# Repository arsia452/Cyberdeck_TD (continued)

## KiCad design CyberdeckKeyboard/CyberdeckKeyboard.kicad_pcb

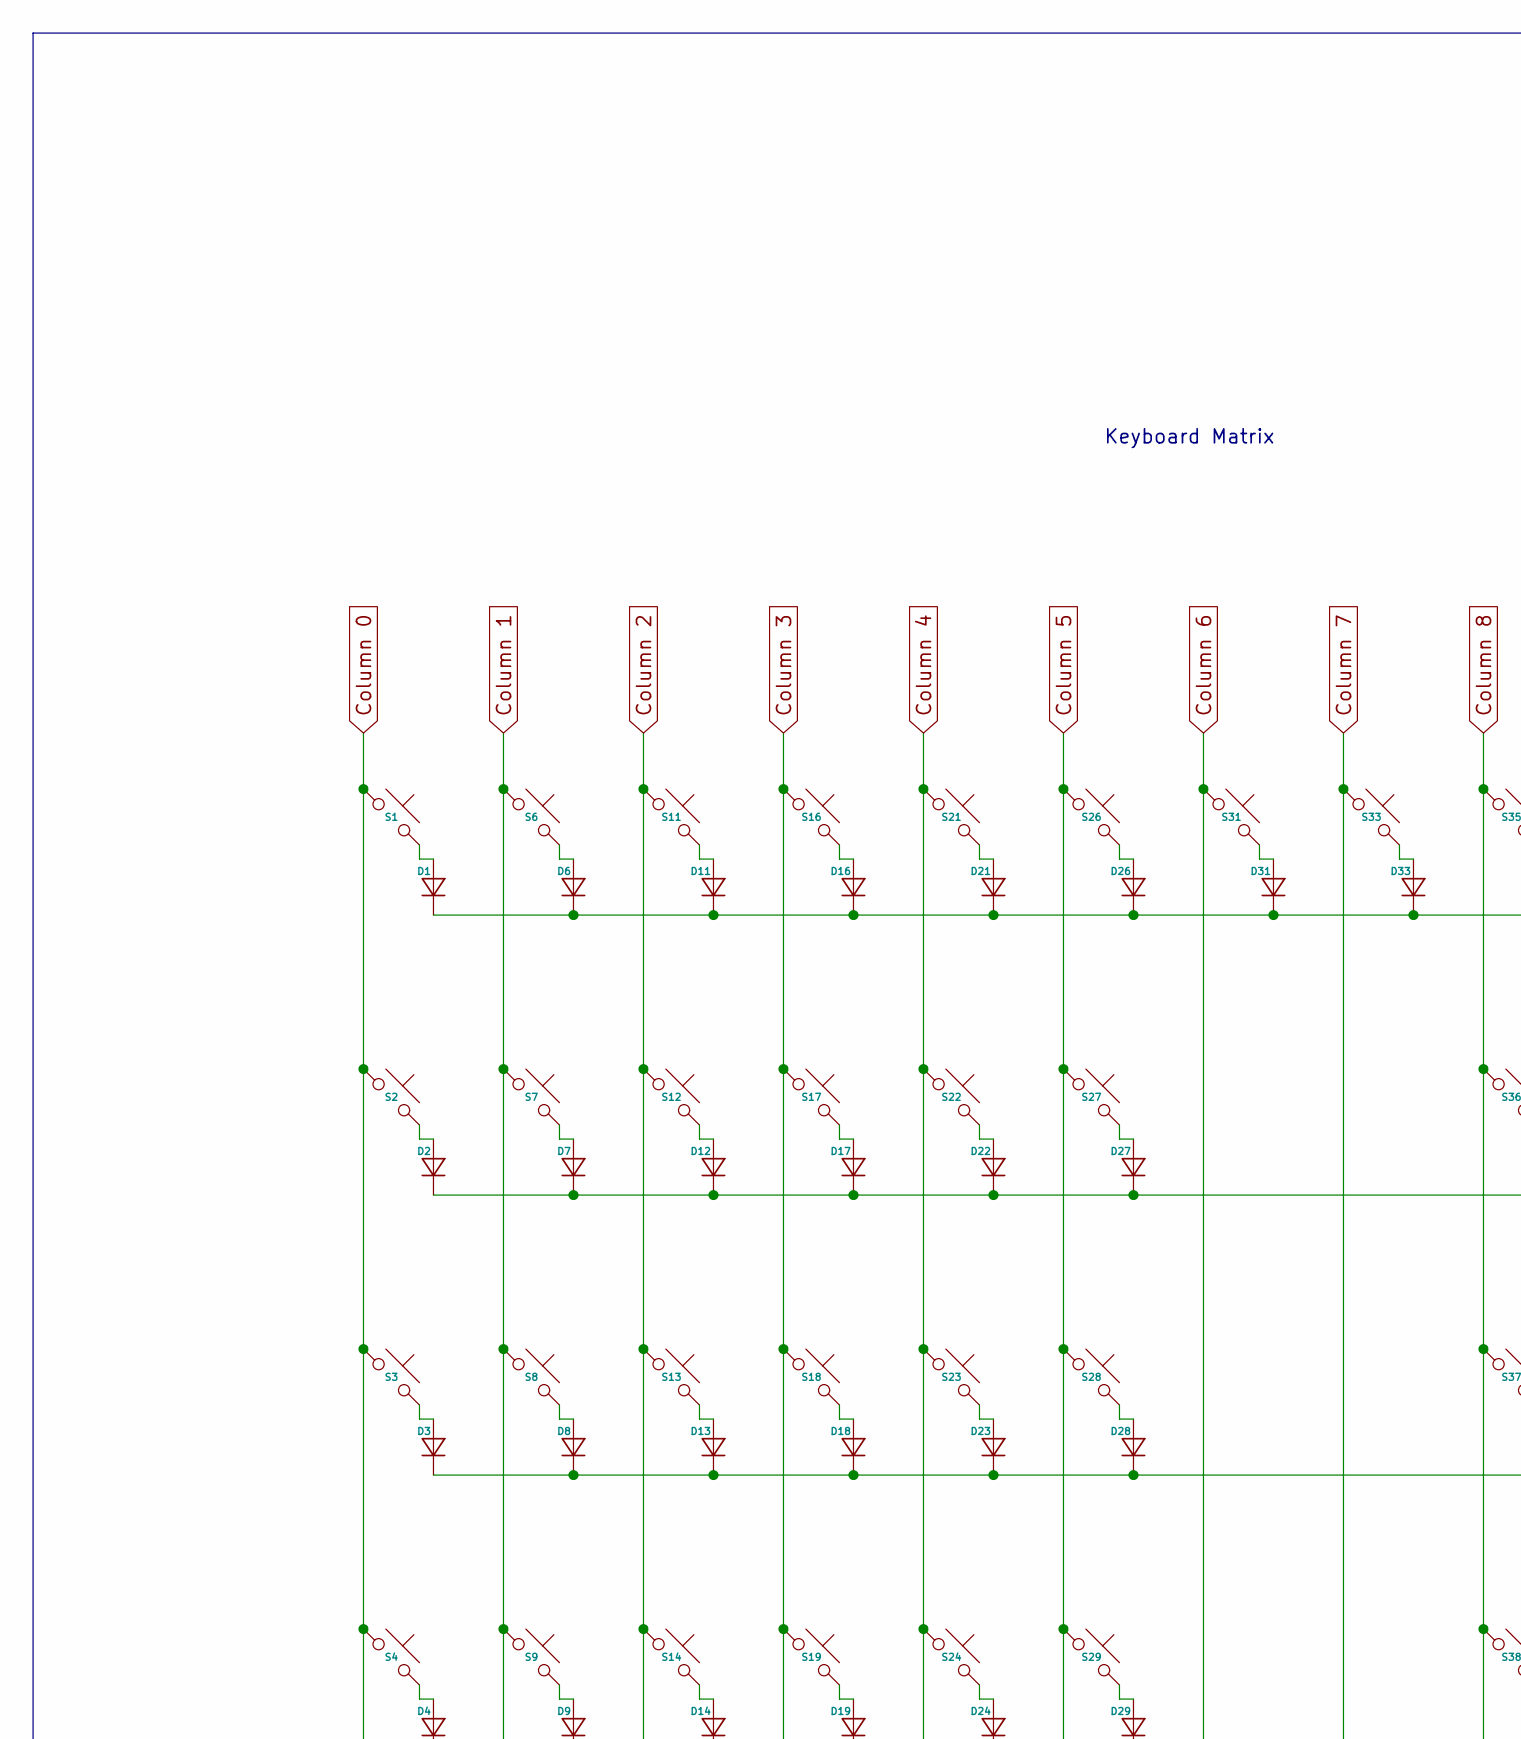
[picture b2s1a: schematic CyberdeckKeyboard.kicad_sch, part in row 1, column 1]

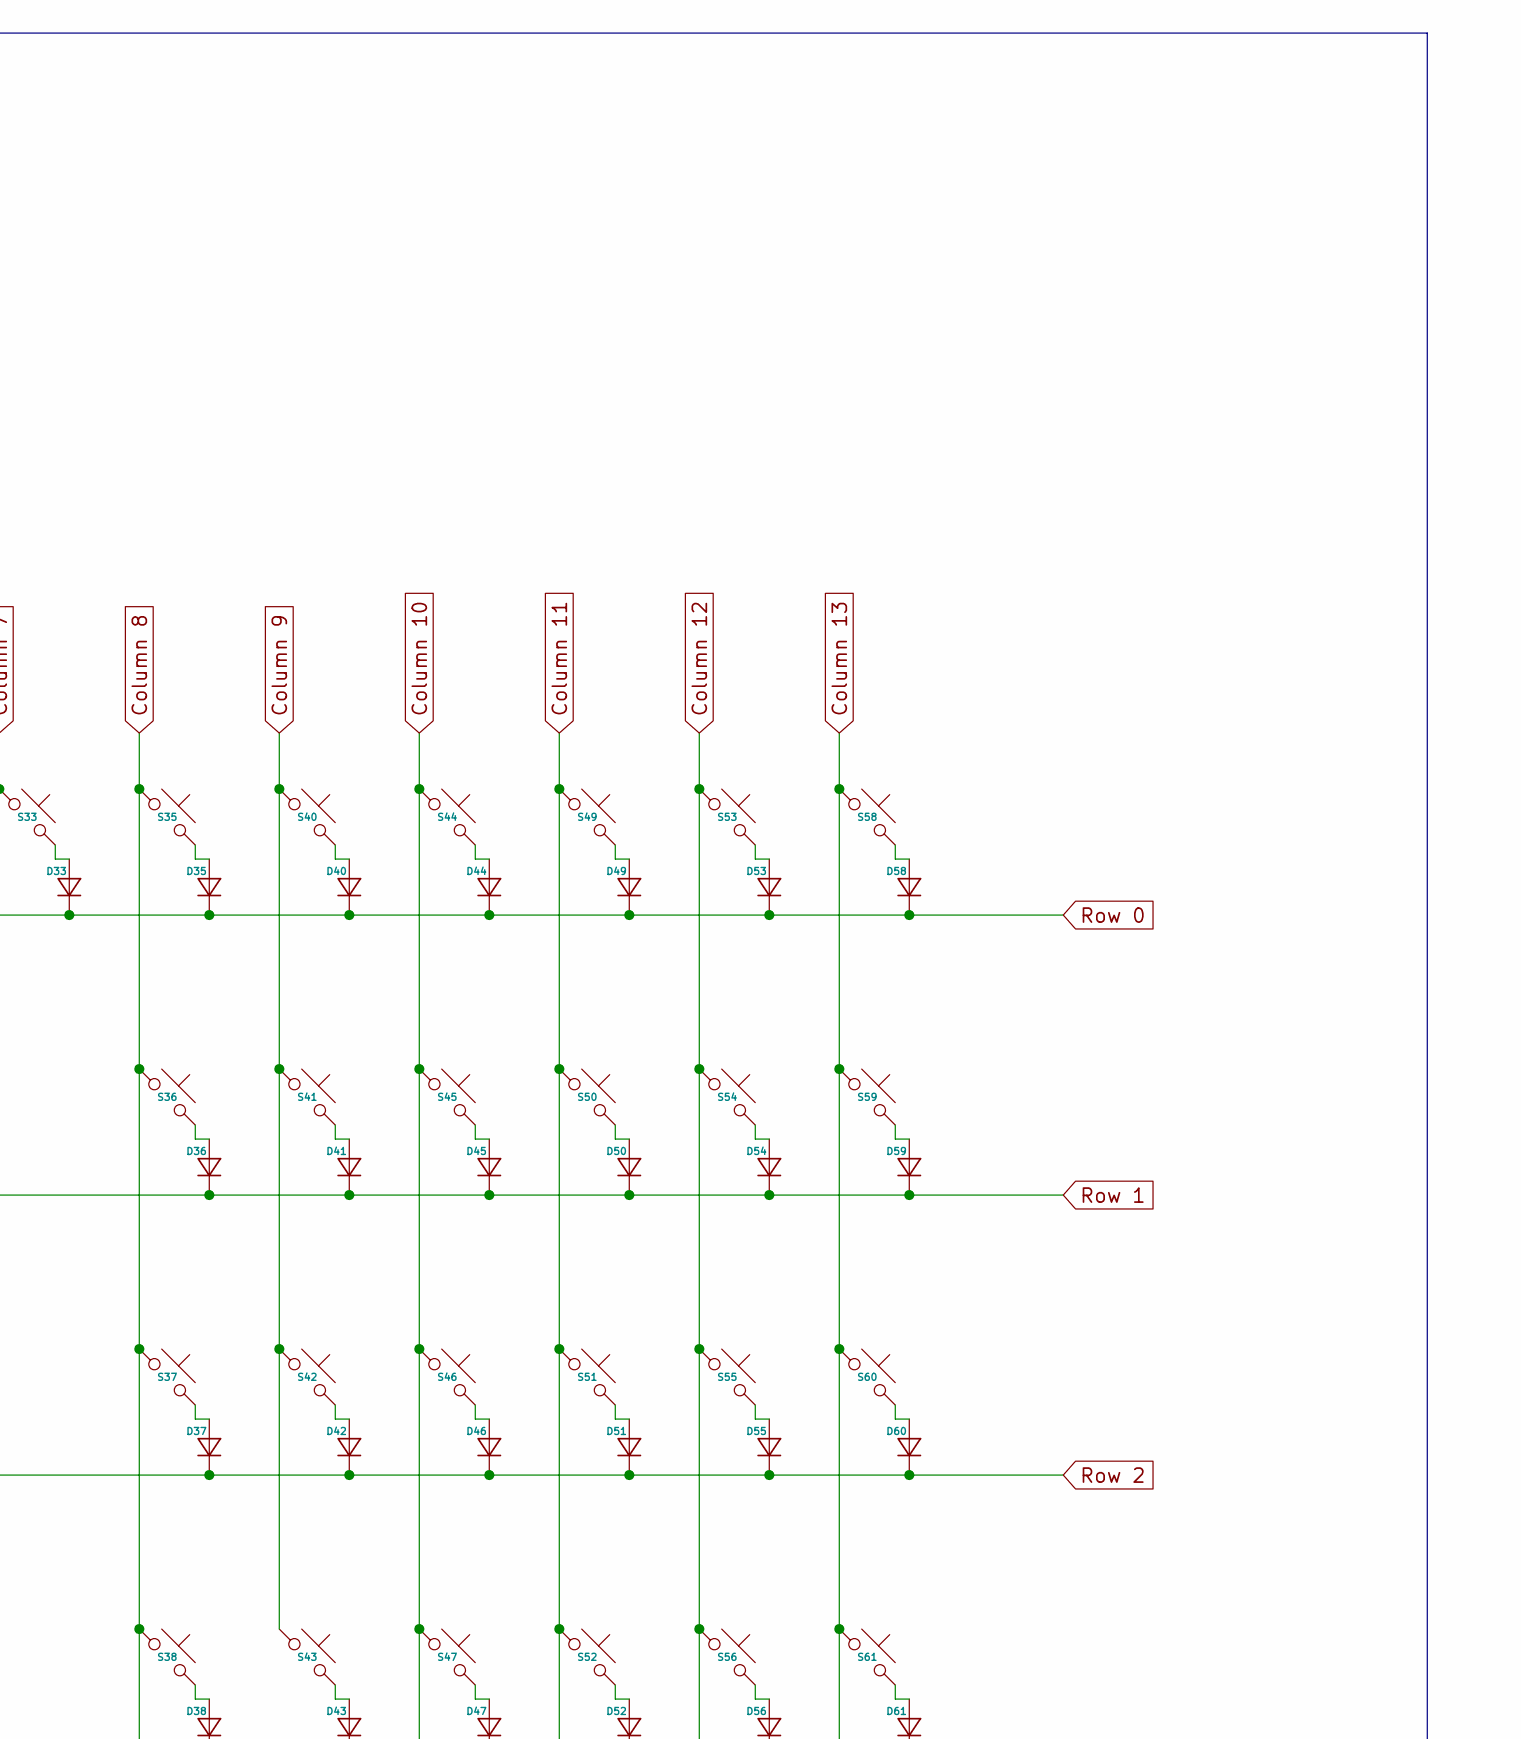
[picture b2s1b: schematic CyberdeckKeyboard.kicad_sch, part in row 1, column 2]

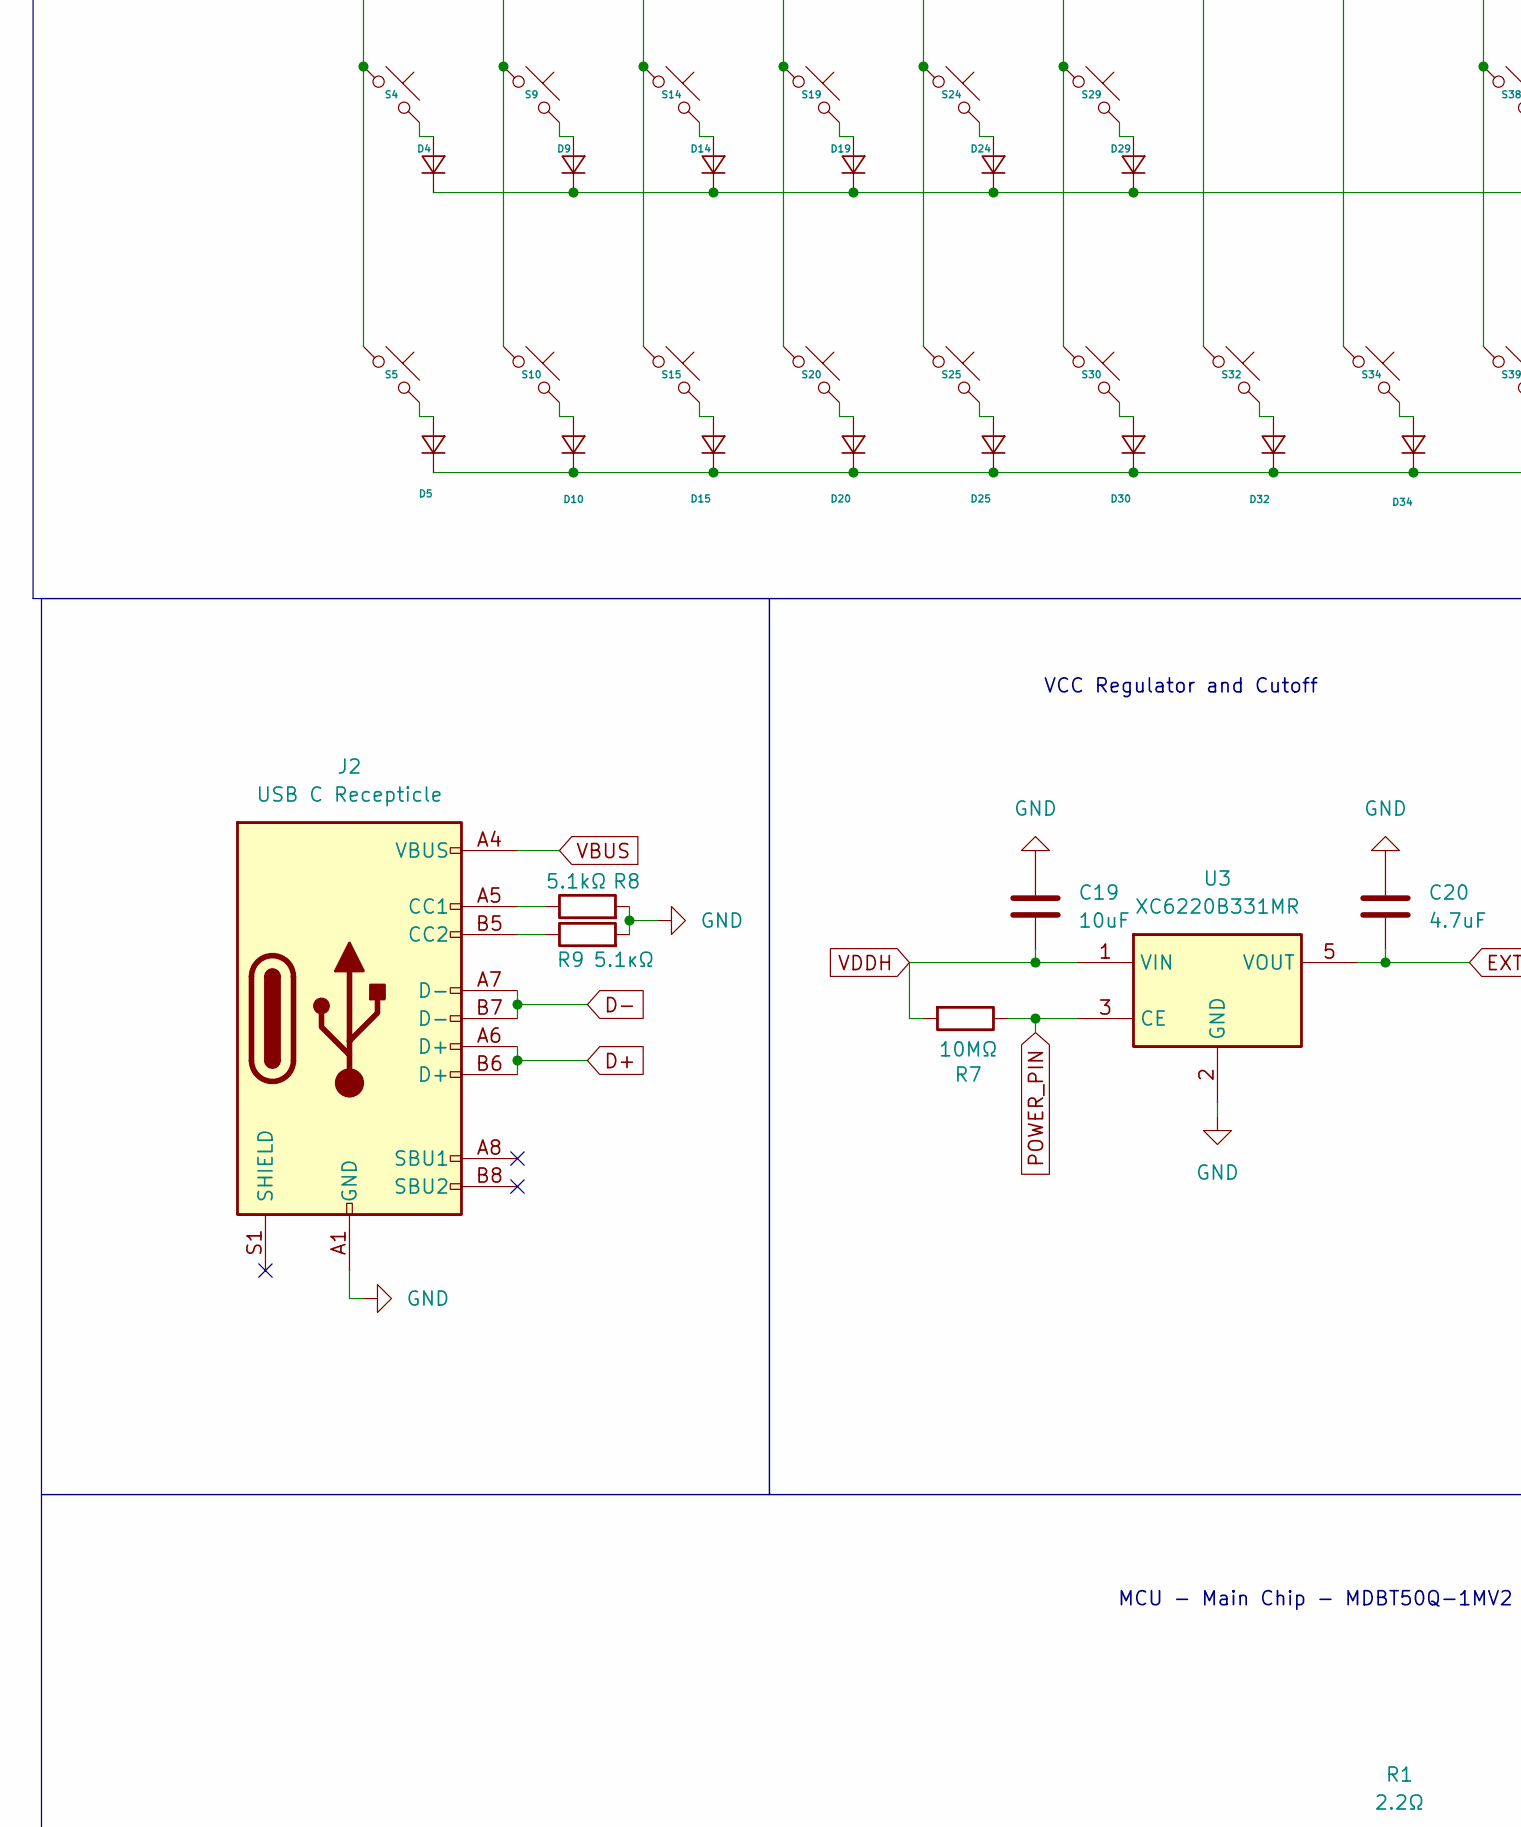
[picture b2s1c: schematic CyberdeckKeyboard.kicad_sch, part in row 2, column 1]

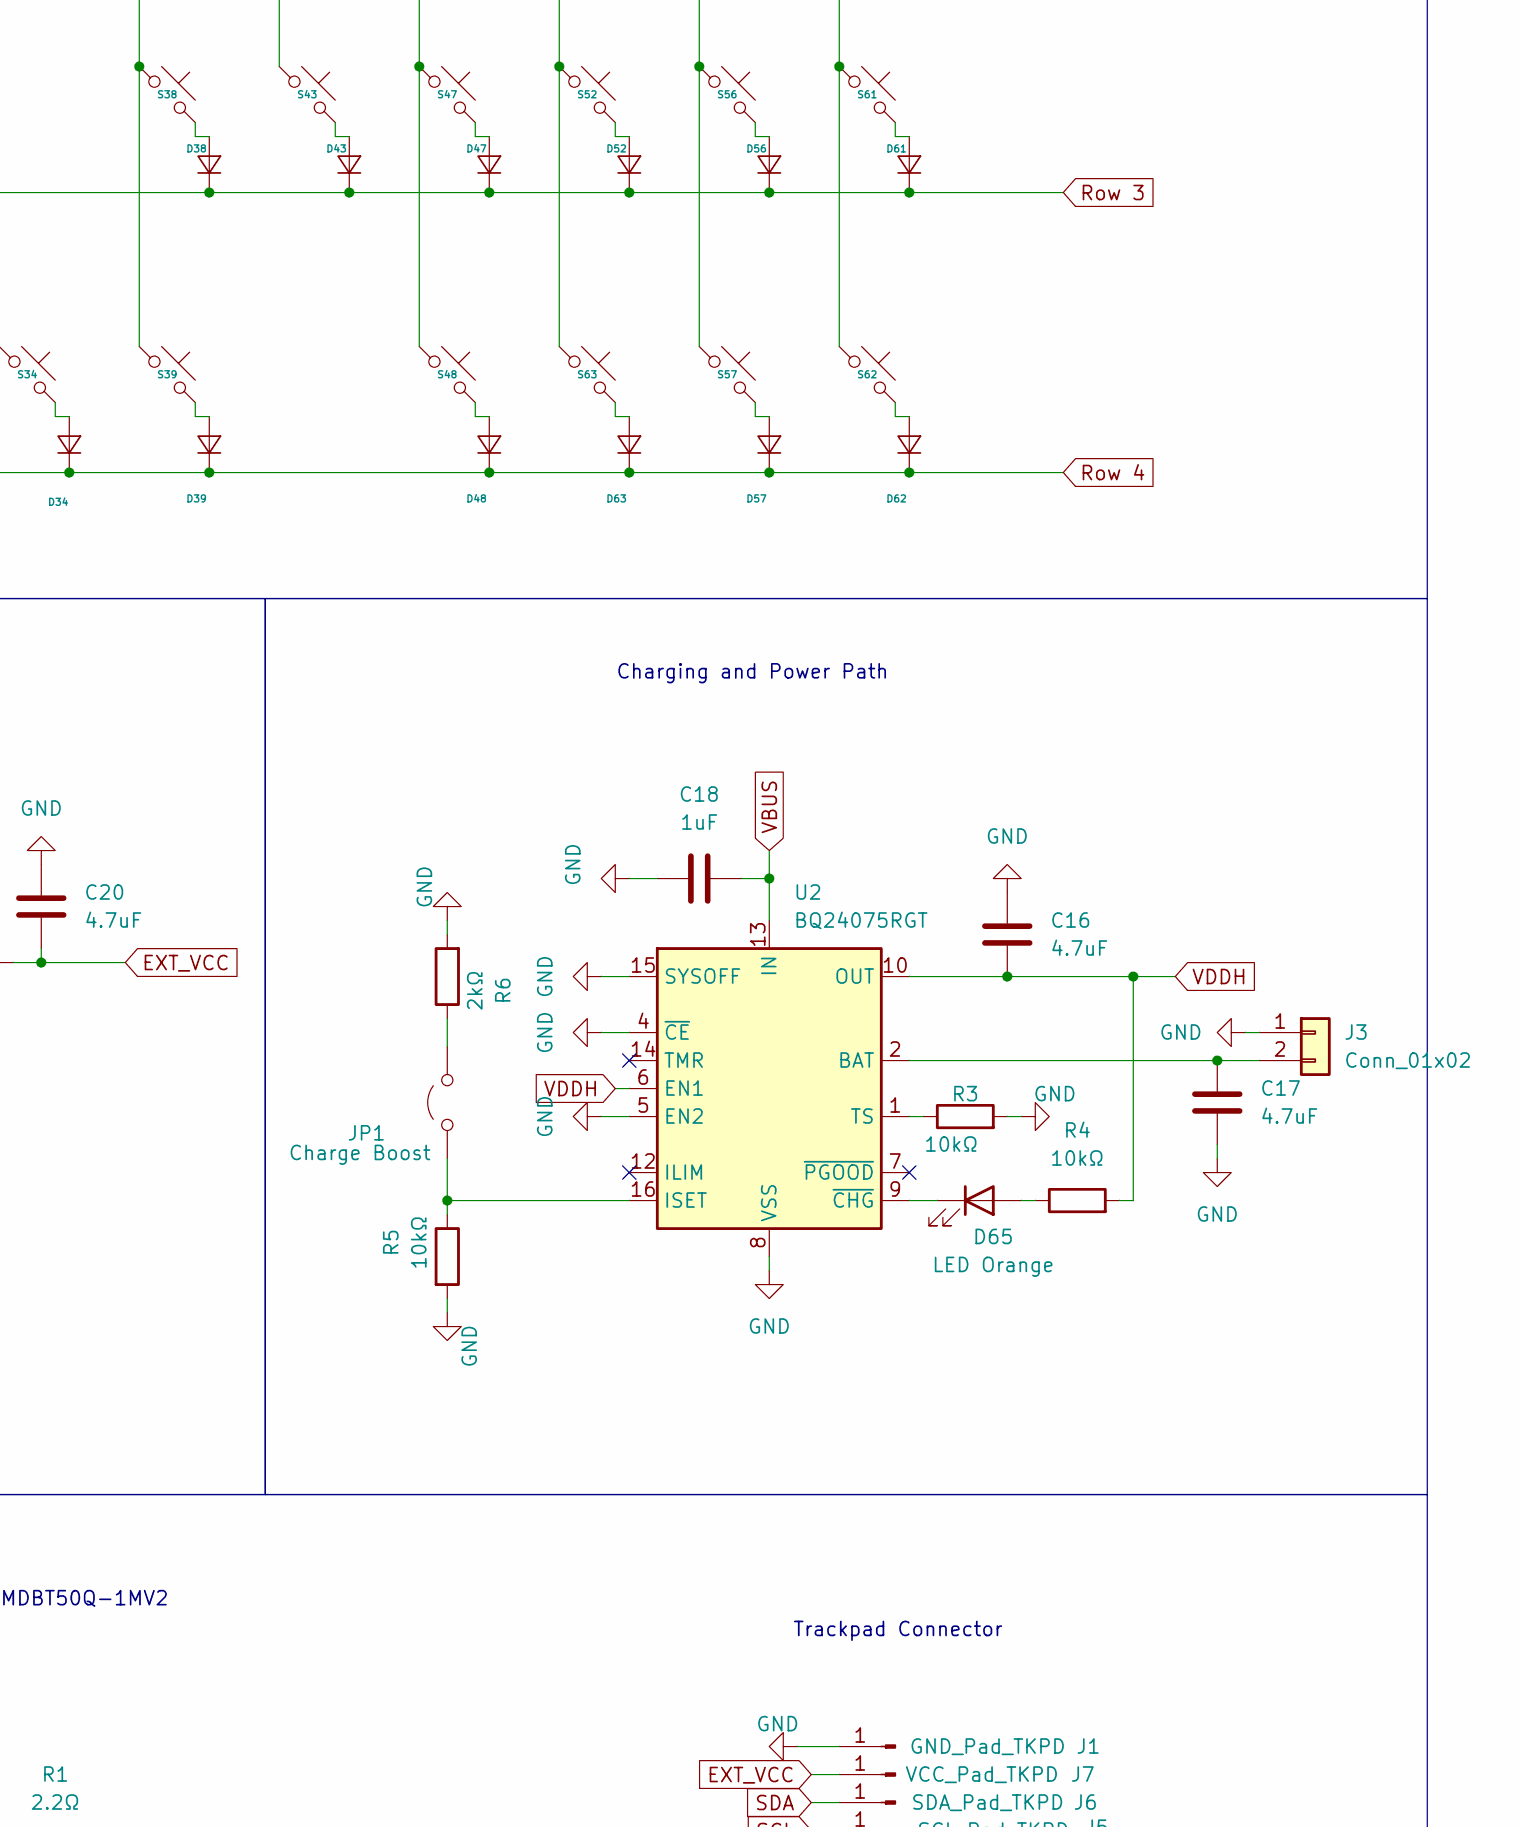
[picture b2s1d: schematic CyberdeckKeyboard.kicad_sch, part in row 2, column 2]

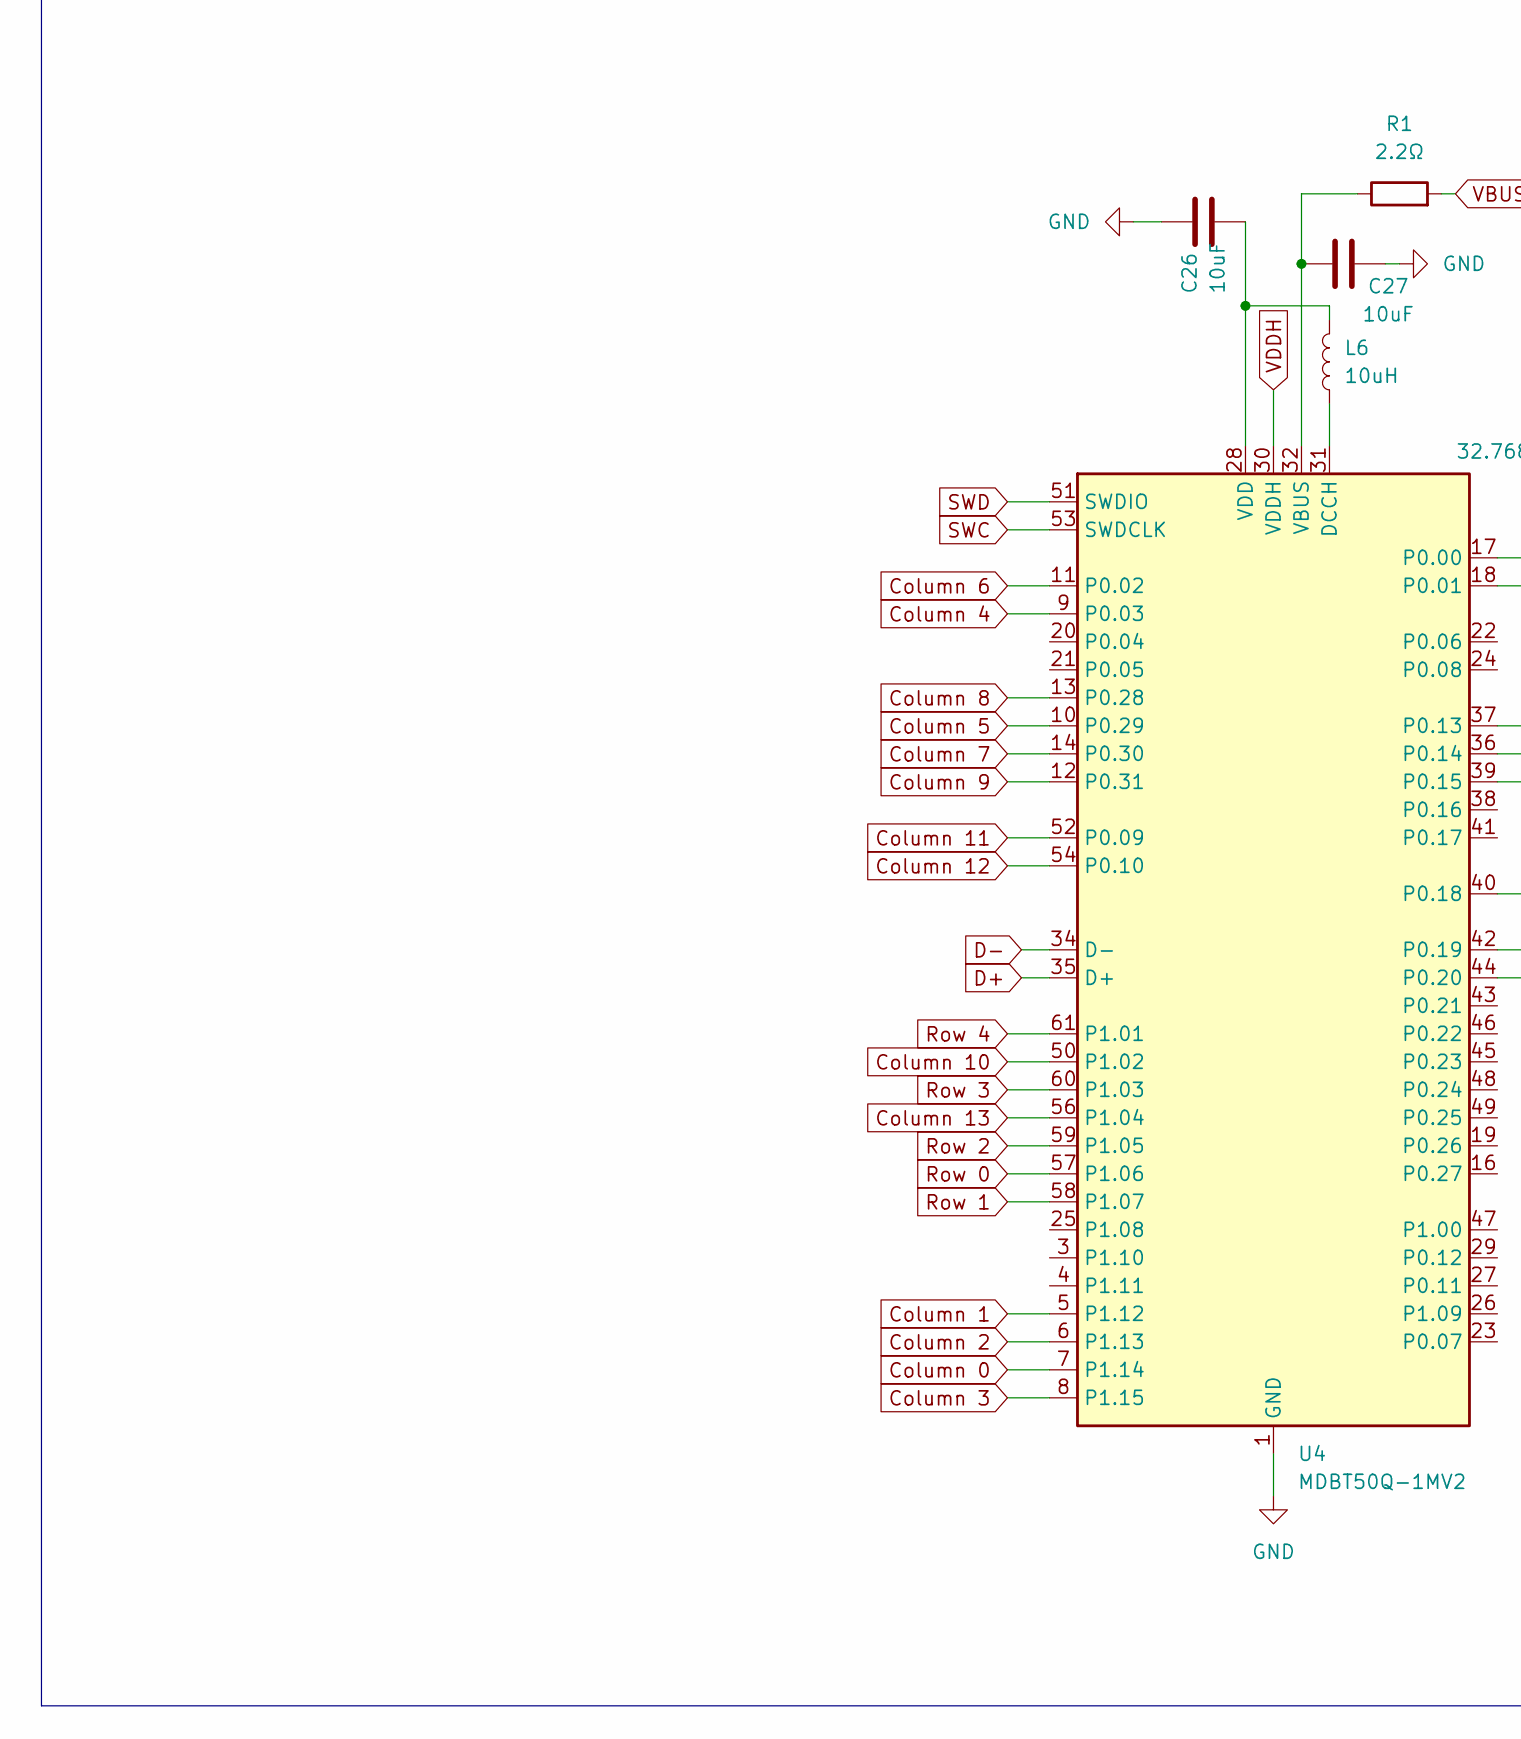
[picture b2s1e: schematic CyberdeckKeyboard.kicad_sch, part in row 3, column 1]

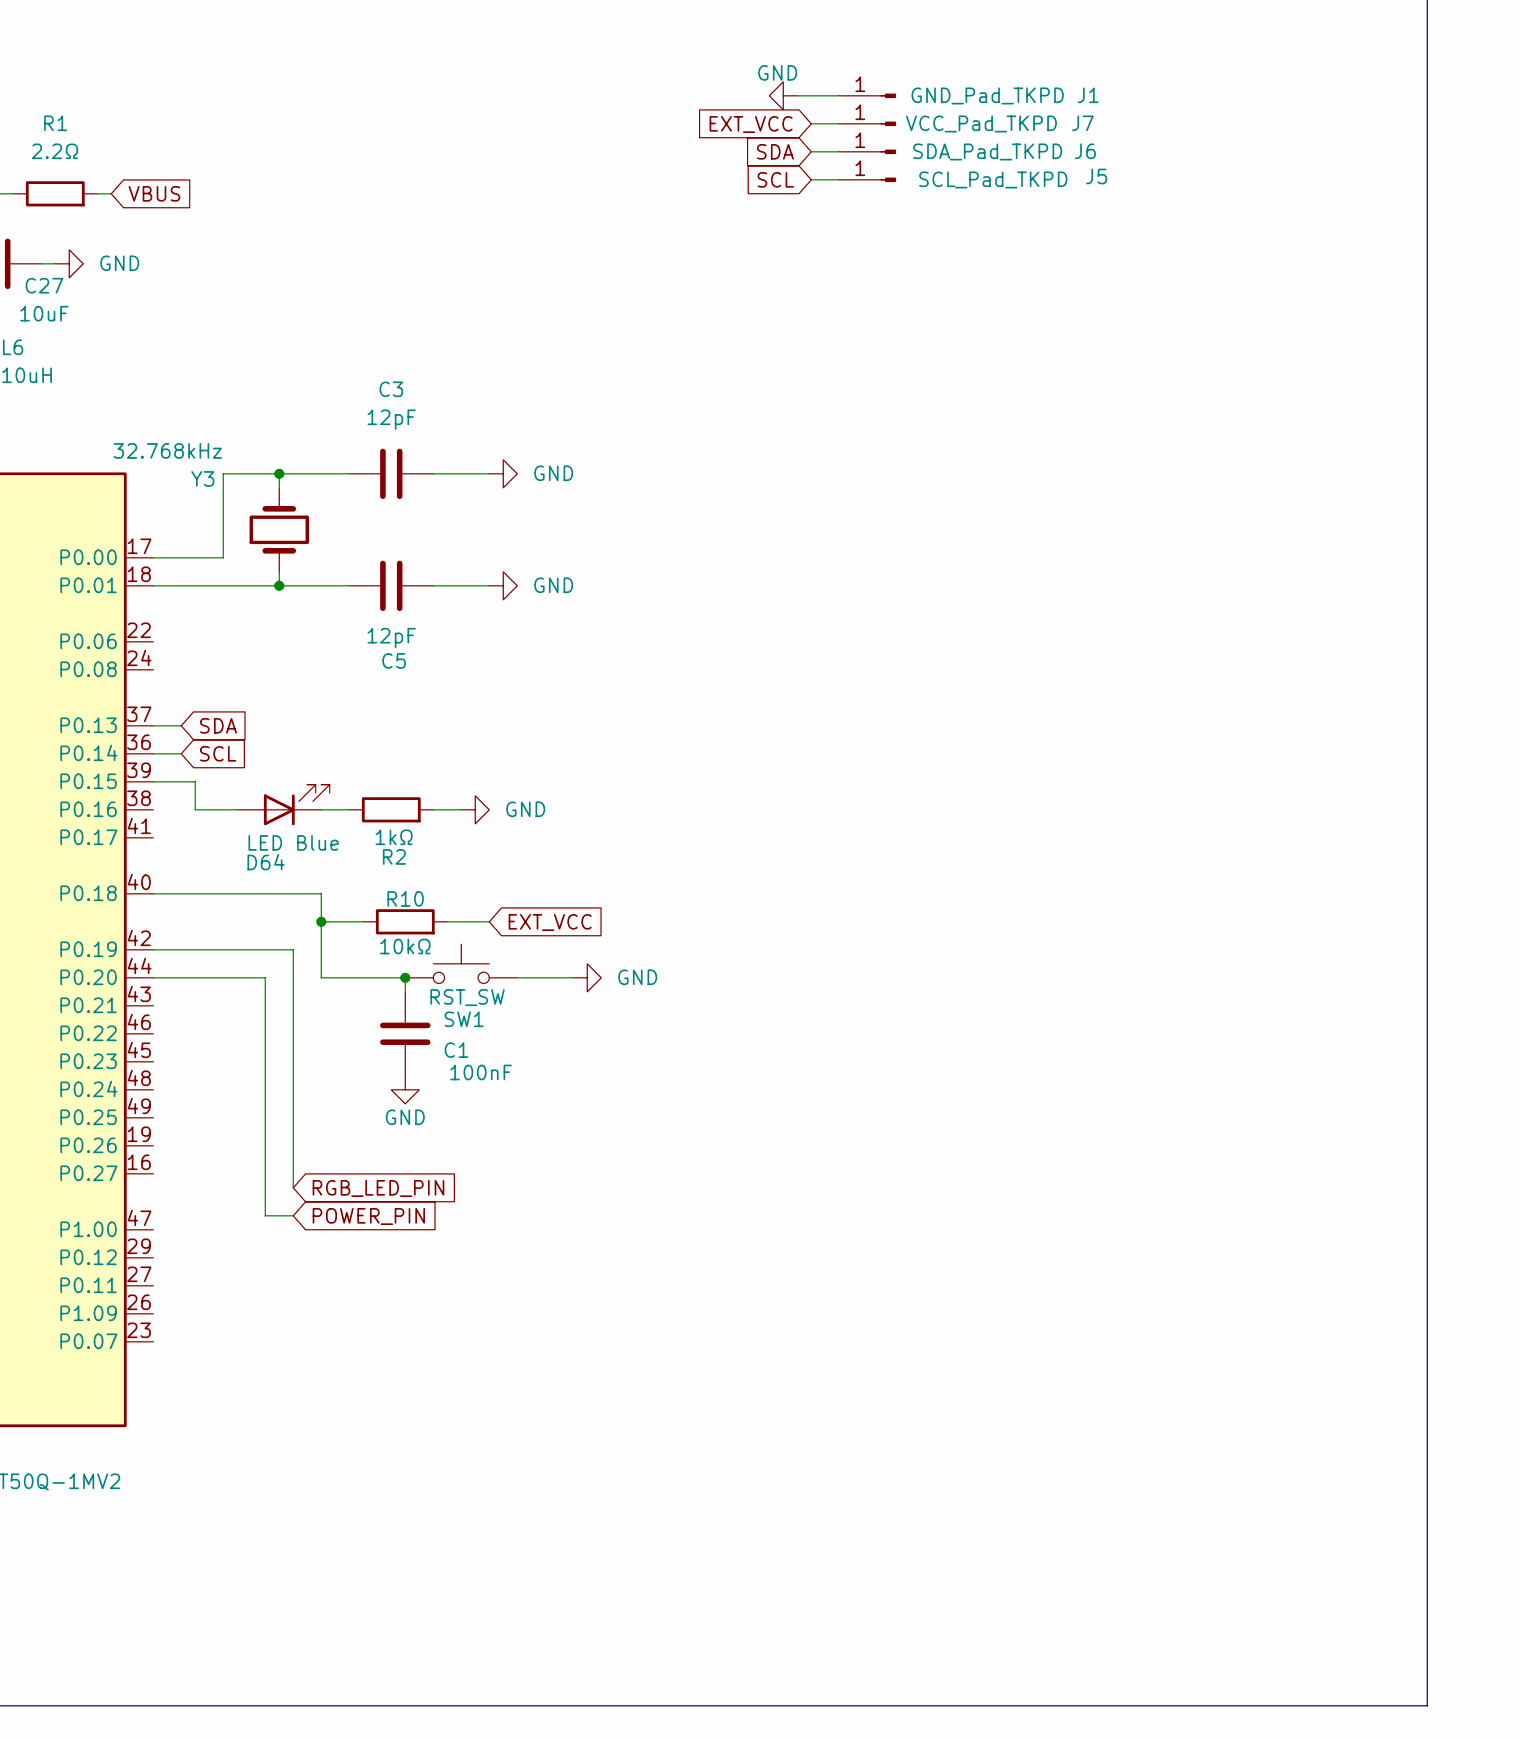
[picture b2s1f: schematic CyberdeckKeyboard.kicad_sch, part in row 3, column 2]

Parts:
C1: 100nF; C_0603_1608Metric
C3, C5: 12pF; C_0603_1608Metric
C16, C17, C20: 4.7uF; C_0603_1608Metric
C18: 1uF; C_0603_1608Metric
C19, C26, C27: 10uF; C_0603_1608Metric
D1, D2, D3, D4, D5, D6, D7, D8, D9, D10, D11, D12, D13, D14, D15, D16, D17, D18, D19, D20, D21, D22, D23, D24, D25, D26, D27, D28, D29, D30, D31, D32, D33, D34, D35, D36, D37, D38, D39, D40, D41, D42, D43, D44, D45, D46, D47, D48, D49, D50, D51, D52, D53, D54, D55, D56, D57, D58, D59, D60, D61, D62, D63: Diode_SOD-123
D64: LED Blue; LED_1206_3216Metric
D65: LED Orange; LED_1206_3216Metric
J1: GND_Pad_TKPD; SolderWirePad_1x01_SMD_2x4mm
J2: USB C Recepticle; USB_C_Receptacle_GCT_USB4105-xx-A_16P_TopMnt_Horizontal
J3: Conn_01x02; JST_PH_B2B-PH-K_1x02_P2.00mm_Vertical
J5: SCL_Pad_TKPD; SolderWirePad_1x01_SMD_2x4mm
J6: SDA_Pad_TKPD; SolderWirePad_1x01_SMD_2x4mm
J7: VCC_Pad_TKPD; SolderWirePad_1x01_SMD_2x4mm
JP1: Charge Boost; SolderJumper-2_P1.3mm_Open_Pad1.0x1.5mm
L6: 10uH; L_0603_1608Metric
R1: 2.2Ω; R_0603_1608Metric
R2: 1kΩ; R_0603_1608Metric
R3, R4, R5, R10: 10kΩ; R_0603_1608Metric
R6: 2kΩ; R_0603_1608Metric
R7: 10MΩ; R_0603_1608Metric
R8: 5.1kΩ; R_0603_1608Metric
R9: 5.1κΩ; R_0603_1608Metric
S1, S2, S3, S4, S5, S6, S7, S8, S9, S10, S11, S12, S13, S14, S15, S16, S17, S18, S19, S20, S21, S22, S23, S24, S25, S26, S27, S28, S29, S30, S31, S33, S35, S36, S37, S38, S39, S40, S41, S42, S43, S44, S45, S46, S47, S48, S49, S50, S51, S52, S53, S54, S55, S56, S57, S58, S59, S60, S61, S62, S63: Choc_V2
S32, S34: SW_PUSH_1P1T_6x3.5mm_H4.3_APEM_MJTP1243
SW1: RST_SW; SW_SPST_CK_RS282G05A3
U2: BQ24075RGT; VQFN-16-1EP_3x3mm_P0.5mm_EP1.6x1.6mm
U3: XC6220B331MR; SOT-23-5
U4: MDBT50Q-1MV2; Raytac_MDBT50Q
Y3: 32.768kHz; Crystal_SMD_2012-2Pin_2.0x1.2mm

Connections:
Column 0: S1.1, S2.1, S3.1, S4.1, S5.1, U4.7 (P1.14)
Column 1: S6.1, S7.1, S8.1, S9.1, S10.1, U4.5 (P1.12)
Column 2: S11.1, S12.1, S13.1, S14.1, S15.1, U4.6 (P1.13)
Column 3: S16.1, S17.1, S18.1, S19.1, S20.1, U4.8 (P1.15)
Column 4: S21.1, S22.1, S23.1, S24.1, S25.1, U4.9 (P0.03)
Column 5: S26.1, S27.1, S28.1, S29.1, S30.1, U4.10 (P0.29)
Column 6: S31.1, S32.1, U4.11 (P0.02)
Column 7: S33.1, S34.1, U4.14 (P0.30)
Column 8: S35.1, S36.1, S37.1, S38.1, S39.1, U4.13 (P0.28)
Column 9: S40.1, S41.1, S42.1, S43.1, U4.12 (P0.31)
Column 10: S44.1, S45.1, S46.1, S47.1, S48.1, U4.50 (P1.02)
Column 11: S49.1, S50.1, S51.1, S52.1, S63.1, U4.52 (P0.09)
Column 12: S53.1, S54.1, S55.1, S56.1, S57.1, U4.54 (P0.10)
Column 13: S58.1, S59.1, S60.1, S61.1, S62.1, U4.56 (P1.04)
D+: J2.A6 (D+), J2.B6 (D+), U4.35 (D+)
D-: J2.A7 (D-), J2.B7 (D-), U4.34 (D-)
EXT_VCC: C20.2, J7.1, R10.2, U3.5 (VOUT)
GND: C1.2, C3.2, C5.2, C16.2, C17.2, C18.2, C19.1, C20.1, C26.1, C27.1, J1.1, J2.A1 (GND), J2.A12 (GND), J2.B1 (GND), J2.B12 (GND), J3.1, R2.2, R3.2, R5.2, R6.2, R8.2, R9.2, SW1.2, U2.4 (~CE), U2.5 (EN2), U2.8 (VSS), U2.15 (SYSOFF), U2.17 (VSS), U3.2 (GND), U4.1 (GND), U4.2 (GND), U4.15 (GND), U4.33 (GND), U4.55 (GND)
unnamed: D1.2 (A), S1.2
unnamed: D2.2 (A), S2.2
unnamed: D3.2 (A), S3.2
unnamed: D4.2 (A), S4.2
unnamed: D5.2 (A), S5.2
unnamed: D6.2 (A), S6.2
unnamed: D7.2 (A), S7.2
unnamed: D8.2 (A), S8.2
unnamed: D9.2 (A), S9.2
unnamed: D10.2 (A), S10.2
unnamed: D11.2 (A), S11.2
unnamed: D12.2 (A), S12.2
unnamed: D13.2 (A), S13.2
unnamed: D14.2 (A), S14.2
unnamed: D15.2 (A), S15.2
unnamed: D16.2 (A), S16.2
unnamed: D17.2 (A), S17.2
unnamed: D18.2 (A), S18.2
unnamed: D19.2 (A), S19.2
unnamed: D20.2 (A), S20.2
unnamed: D21.2 (A), S21.2
unnamed: D22.2 (A), S22.2
unnamed: D23.2 (A), S23.2
unnamed: D24.2 (A), S24.2
unnamed: D25.2 (A), S25.2
unnamed: D26.2 (A), S26.2
unnamed: D27.2 (A), S27.2
unnamed: D28.2 (A), S28.2
unnamed: D29.2 (A), S29.2
unnamed: D30.2 (A), S30.2
unnamed: D31.2 (A), S31.2
unnamed: D32.2 (A), S32.2
unnamed: D33.2 (A), S33.2
unnamed: D34.2 (A), S34.2
unnamed: D35.2 (A), S35.2
unnamed: D36.2 (A), S36.2
unnamed: D37.2 (A), S37.2
unnamed: D38.2 (A), S38.2
unnamed: D39.2 (A), S39.2
unnamed: D40.2 (A), S40.2
unnamed: D41.2 (A), S41.2
unnamed: D42.2 (A), S42.2
unnamed: D43.2 (A), S43.2
unnamed: D44.2 (A), S44.2
unnamed: D45.2 (A), S45.2
unnamed: D46.2 (A), S46.2
unnamed: D47.2 (A), S47.2
unnamed: D48.2 (A), S48.2
unnamed: D49.2 (A), S49.2
unnamed: D50.2 (A), S50.2
unnamed: D51.2 (A), S51.2
unnamed: D52.2 (A), S52.2
unnamed: D53.2 (A), S53.2
unnamed: D54.2 (A), S54.2
unnamed: D55.2 (A), S55.2
unnamed: D56.2 (A), S56.2
unnamed: D57.2 (A), S57.2
unnamed: D58.2 (A), S58.2
unnamed: D59.2 (A), S59.2
unnamed: D60.2 (A), S60.2
unnamed: D61.2 (A), S61.2
unnamed: D62.2 (A), S62.2
unnamed: D63.2 (A), S63.2
unnamed: D64.2 (A), U4.39 (P0.15)
unnamed: D64.1 (K), R2.1
unnamed: D65.2 (A), R4.1
unnamed: D65.1 (K), U2.9 (~CHG)
unnamed: J2.A5 (CC1), R8.1
unnamed: J2.B5 (CC2), R9.1
unnamed: C17.1, J3.2, U2.2 (BAT), U2.3 (BAT)
unnamed: JP1.1 (A), R5.1, U2.16 (ISET)
unnamed: JP1.2 (B), R6.1
unnamed: R3.1, U2.1 (TS)
unnamed: L6.1, U4.31 (DCCH)
unnamed: C3.1, U4.17 (P0.00), Y3.2
unnamed: C5.1, U4.18 (P0.01), Y3.1
unnamed: C1.1, R10.1, SW1.1, U4.40 (P0.18)
unnamed: C27.2, R1.1, U4.32 (VBUS)
unnamed: C26.2, L6.2, U4.28 (VDD)
POWER_PIN: R7.1, U3.3 (CE), U4.44 (P0.20)
RGB_LED_PIN: U4.42 (P0.19)
Row 0: D1.1 (K), D6.1 (K), D11.1 (K), D16.1 (K), D21.1 (K), D26.1 (K), D31.1 (K), D33.1 (K), D35.1 (K), D40.1 (K), D44.1 (K), D49.1 (K), D53.1 (K), D58.1 (K), U4.57 (P1.06)
Row 1: D2.1 (K), D7.1 (K), D12.1 (K), D17.1 (K), D22.1 (K), D27.1 (K), D36.1 (K), D41.1 (K), D45.1 (K), D50.1 (K), D54.1 (K), D59.1 (K), U4.58 (P1.07)
Row 2: D3.1 (K), D8.1 (K), D13.1 (K), D18.1 (K), D23.1 (K), D28.1 (K), D37.1 (K), D42.1 (K), D46.1 (K), D51.1 (K), D55.1 (K), D60.1 (K), U4.59 (P1.05)
Row 3: D4.1 (K), D9.1 (K), D14.1 (K), D19.1 (K), D24.1 (K), D29.1 (K), D38.1 (K), D43.1 (K), D47.1 (K), D52.1 (K), D56.1 (K), D61.1 (K), U4.60 (P1.03)
Row 4: D5.1 (K), D10.1 (K), D15.1 (K), D20.1 (K), D25.1 (K), D30.1 (K), D32.1 (K), D34.1 (K), D39.1 (K), D48.1 (K), D57.1 (K), D62.1 (K), D63.1 (K), U4.61 (P1.01)
SCL: J5.1, U4.36 (P0.14)
SDA: J6.1, U4.37 (P0.13)
SWC: U4.53 (SWDCLK)
SWD: U4.51 (SWDIO)
VBUS: C18.1, J2.A4 (VBUS), J2.A9 (VBUS), J2.B4 (VBUS), J2.B9 (VBUS), R1.2, U2.13 (IN)
VDDH: C16.1, C19.2, R4.2, R7.2, U2.6 (EN1), U2.10 (OUT), U2.11 (OUT), U3.1 (VIN), U4.30 (VDDH)

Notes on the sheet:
Keyboard Matrix
Charging and Power Path
VCC Regulator and Cutoff
Trackpad Connector
MCU - Main Chip - MDBT50Q-1MV2

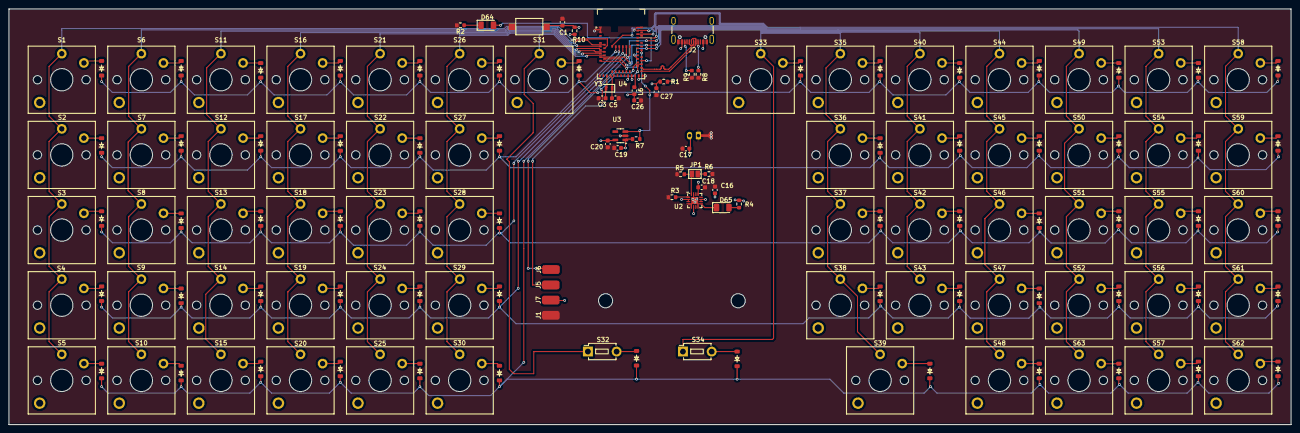
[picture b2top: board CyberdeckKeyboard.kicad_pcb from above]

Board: 4 copper layers, 290.0 x 94.0 mm, 161 parts (1 on the bottom side), 107 nets.

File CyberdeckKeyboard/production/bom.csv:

Designator,Footprint,Quantity,Value,LCSC Part #
C1,0603,1,100nF,
"C16, C17, C20",0603,3,4.7uF,
C18,0603,1,1uF,
"C19, C26, C27",0603,3,10uF,
"C3, C5",0603,2,12pF,
"D1, D10, D11, D12, D13, D14, D15, D16, D17, D18, D19, D2, D20, D21, D22, D23, D24, D25, D26, D27, D28, D29, D3, D30, D31, D32, D33, D34, D35, D36, D37, D38, D39, D4, D40, D41, D42, D43, D44, D45, D46, D47, D48, D49, D5, D50, D51, D52, D53, D54, D55, D56, D57, D58, D59, D6, D60, D61, D62, D63, D7, D8, D9",Diode_SOD-123,63,~,
D64,1206,1,LED Blue,
D65,1206,1,LED Orange,
J1,SolderWirePad_1x01_SMD_2x4mm,1,GND_Pad_TKPD,
J2,USB_C_Receptacle_GCT_USB4105-xx-A_16P_TopMnt_Horizontal,1,USB C Recepticle,
J3,JST_PH_B2B-PH-K_1x02_P2.00mm_Vertical,1,Conn_01x02,
J5,SolderWirePad_1x01_SMD_2x4mm,1,SCL_Pad_TKPD,
J6,SolderWirePad_1x01_SMD_2x4mm,1,SDA_Pad_TKPD,
J7,SolderWirePad_1x01_SMD_2x4mm,1,VCC_Pad_TKPD,
JP1,SolderJumper-2_P1.3mm_Open_Pad1.0x1.5mm,1,Charge Boost,
L6,0603,1,10uH,
R1,0603,1,2.2Ω,
"R10, R3, R4, R5",0603,4,10kΩ,
R2,0603,1,1kΩ,
R6,0603,1,2kΩ,
R7,0603,1,10MΩ,
R8,0603,1,5.1kΩ,
R9,0603,1,5.1κΩ,
"S1, S10, S11, S12, S13, S14, S15, S16, S17, S18, S19, S2, S20, S21, S22, S23, S24, S25, S26, S27, S28, S29, S3, S30, S31, S33, S35, S36, S37, S38, S39, S4, S40, S41, S42, S43, S44, S45, S46, S47, S48, S49, S5, S50, S51, S52, S53, S54, S55, S56, S57, S58, S59, S6, S60, S61, S62, S63, S7, S8, S9",Choc_V1V2_1.00u,61,~,
SW1,SW_SPST_CK_RS282G05A3,1,RST_SW,
U2,VQFN-16-1EP_3x3mm_P0.5mm_EP1.6x1.6mm,1,BQ24075RGT,
U3,SOT-23-5,1,XC6220B331MR,
Y3,Crystal_SMD_2012-2Pin_2.0x1.2mm,1,32.768kHz FC-12M,
